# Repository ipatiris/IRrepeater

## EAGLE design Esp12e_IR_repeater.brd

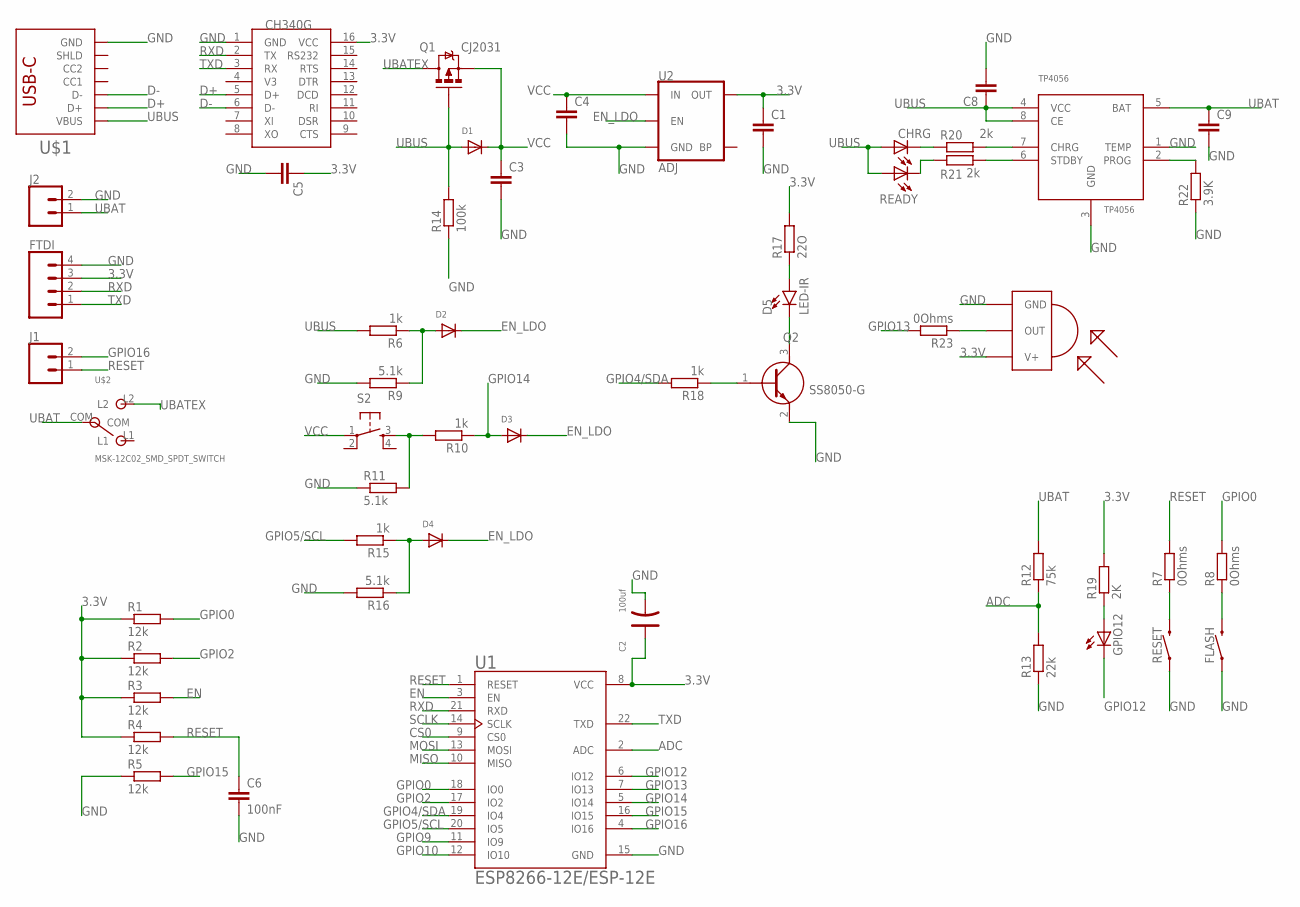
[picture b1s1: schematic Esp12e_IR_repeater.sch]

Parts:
C1, C3, C4, C5: 1uF; CAPC1608X85
C2: 100uf; AVX-B
C6: 100nF; C0805
C8, C9: 10uF; CAPC1608X85
CHRG: LEDCHIPLED_0805; CHIPLED_0805
D1, D2, D3, D4: DIODESOD-123; SOD-123
D5: LED-IR; LED_5MM
FLASH: RS032G05A3SM-SPST-MOMENTARY-SWSMD-1101NE; TACTILE-SWITCH-1101NE
FTDI: CONN_04; 1X04
GPIO12: LEDCHIPLED_0805; CHIPLED_0805
J1: CONN_02; 1X02
J2: CONN_02-JST-2-PTH-NO_SILK; JST-2-PTH-NS
Q1: CJ2031; SOT23-3
Q2: SS8050-G; SOT95P240X115-3N
R1, R2, R3, R4, R5: 12k; R0603
R6, R10, R15, R18: 1k; R0603
R7, R8, R23: 0Ohms; R0603
R9, R11, R16: 5.1k; R0603
R12: 75k; R0603
R13: 22k; R0603
R14: 100k; R0603
R17: 22O; R0603
R19: 2K; R0603
R20, R21: 2k; R0603
R22: 3.9K; R0603
READY: LEDCHIPLED_0805; CHIPLED_0805
RESET: RS032G05A3SM-SPST-MOMENTARY-SWSMD-1101NE; TACTILE-SWITCH-1101NE
S2: SWITCH-TACT_DTSM-6
TP4056: TP4056; SOP-8
U1: ESP8266-12E/ESP-12E; XCVR_ESP8266-12E/ESP-12E
U2: ADJ; SOT23-5
U$1: MOEKOE_USB_C_C393939; MOEKOE_USBC_C393939
U$2: MSK-12C02_SMD_SPDT_SWITCH; MSK-12C02
U$3: CH340G; SOIC16
U$4: TSOP1738; TSOP17XX

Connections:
3.3V: C1.1, C2.+, C5.1, FTDI.3, R1.1, R2.1, R3.1, R4.1, R17.2, R19.2, U1.8 (VCC), U2.5 (OUT), U$3.16 (VCC), U$4.V+
ADC: R12.1, R13.2, U1.2 (ADC)
CS0: U1.9 (CS0)
D+: U$1.A6 (D+), U$1.B6 (D+), U$3.5 (D+)
D-: U$1.A7 (D-), U$1.B7 (D-), U$3.6 (D-)
EN: R3.2, U1.3 (EN)
EN_LDO: D2.C, D3.C, D4.C, U2.3 (EN)
GND: C1.2, C2.-, C3.2, C4.2, C5.2, C6.2, C8.2, C9.2, FLASH.1, FTDI.4, J2.2, Q2.2 (E), R5.1, R9.2, R11.1, R13.1, R14.1, R16.2, R22.1, RESET.1, TP4056.1 (TEMP), TP4056.3 (GND), U1.15 (GND), U2.2 (GND), U$1.A1B12 (GND), U$1.B1A12 (GND), U$3.1 (GND), U$4.GND
GPIO0: R1.2, R8.2, U1.18 (IO0)
GPIO2: R2.2, U1.17 (IO2)
GPIO4/SDA: R18.2, U1.19 (IO4)
GPIO5/SCL: R15.2, U1.20 (IO5)
GPIO9: U1.11 (IO9)
GPIO10: U1.12 (IO10)
GPIO12: GPIO12.C, U1.6 (IO12)
GPIO13: R23.2, U1.7 (IO13)
GPIO14: D3.A, R10.1, U1.5 (IO14)
GPIO15: R5.2, U1.16 (IO15)
GPIO16: J1.2, U1.4 (IO16)
MISO: U1.10 (MISO)
MOSI: U1.13 (MOSI)
unnamed: FLASH.2, R8.1
unnamed: R7.1, RESET.2
unnamed: D2.A, R6.1, R9.1
unnamed: D4.A, R15.1, R16.1
unnamed: R20.2, TP4056.7 (CHRG)
unnamed: R10.2, R11.2, S2.3
unnamed: D5.A, R17.1
unnamed: D5.K (C), Q2.3 (C)
unnamed: Q2.1 (B), R18.1
unnamed: GPIO12.A, R19.1
unnamed: R21.2, TP4056.6 (STDBY)
unnamed: CHRG.C, R20.1
unnamed: R21.1, READY.C
unnamed: R22.2, TP4056.2 (PROG)
unnamed: R23.1, U$4.OUT
RESET: C6.1, J1.1, R4.2, R7.2, U1.1 (RESET)
RXD: FTDI.2, U1.21 (RXD), U$3.2 (TX)
SCLK: U1.14 (SCLK)
TXD: FTDI.1, U1.22 (TXD), U$3.3 (RX)
UBAT: C9.1, J2.1, R12.2, TP4056.5 (BAT), U$2.COM
UBATEX: Q1.3 (D), U$2.L2
UBUS: C8.1, CHRG.A, D1.A, Q1.1 (G), R6.2, R14.2, READY.A, TP4056.4 (VCC), TP4056.8 (CE), U$1.A4B9 (VBUS), U$1.B4A9 (VBUS)
VCC: C3.1, C4.1, D1.C, Q1.2 (S), S2.1, U2.1 (IN)

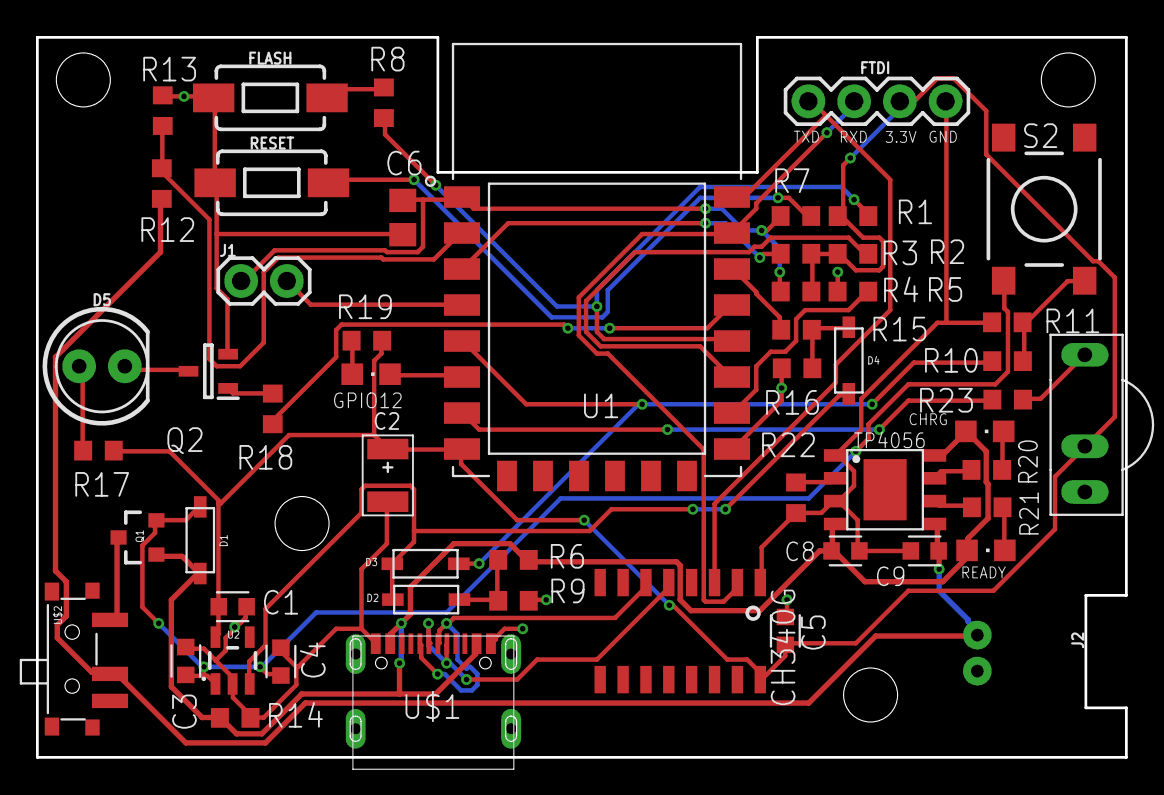
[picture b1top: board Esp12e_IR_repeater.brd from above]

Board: 2 copper layers, 60.5 x 40.0 mm, 54 parts (0 on the bottom side), 38 nets.

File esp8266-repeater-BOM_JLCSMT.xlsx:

Comment | Designator | Footprint | JLCPCB Part #（optional）
1uF | C1 | C0603 | C15849
100uF | C2 | CASE-B_3528 | C16133
1uF | C3 | C0603 | C15849
1uF | C4 | C0603 | C15849
1uF | C5 | C0603 | C15849
100nF | C6 | C0805 | C49678
10uF | C8 | C0603 | C19702
10uF | C9 | C0603 | C19702
CHRG LED | CHRG | LED_0805 | C84256
DIODE | D1 | SOD-123 | C8598
DIODE | D2 | SOD-123 | C8598
DIODE | D3 | SOD-123 | C8598
DIODE | D4 | SOD-123 | C8598
GPIO12 LED | GPIO12 | LED_0805 | C84256
IR TRANS | Q2 | SOT-23-3 | C2150
12K | R1 | R0603 | C22790
12K | R2 | R0603 | C22790
12K | R3 | R0603 | C22790
12K | R4 | R0603 | C22790
12K | R5 | R0603 | C22790
1K | R6 | R0603 | C21190
0Ohms | R7 | R0603 | C21189
0Ohms | R8 | R0603 | C21189
5.1K | R9 | R0603 | C25197
1K | R10 | R0603 | C21190
5.1K | R11 | R0603 | C25197
75K | R12 | R0603 | C23242
22K | R13 | R0603 | C31850
100K | R14 | R0603 | C25803
1K | R15 | R0603 | C21190
5.1K | R16 | R0603 | C25197
100Ohms | R17 | R0603 | C22775
1K | R18 | R0603 | C21190
2K | R19 | R0603 | C22975
2K | R20 | R0603 | C22975
2K | R21 | R0603 | C22975
3.9K | R22 | R0603 | C23018
0Ohms | R23 | R0603 | C21189
READY LED | READY | LED_0805 | C2297
CHARGER IC | TP4056 | ESOP-8_EP_3.9x4.9x1.27P | C16581
USB C | U$1 | SMD | C393939
CH340G | U$3 | SOIC-16_3.9x9.9x1.27P | C14267
ESP8266 | U1 | DFN-22_16.0x24.0x2.0P | C82891
ME6211 | U2 | SOT-23-5 | C82942

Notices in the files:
parts and their libraries:
SparkFun-IC-Power: Licensing: Creative Commons ShareAlike 4.0 International - https://creativecommons.org/licenses/by-sa/4.0
